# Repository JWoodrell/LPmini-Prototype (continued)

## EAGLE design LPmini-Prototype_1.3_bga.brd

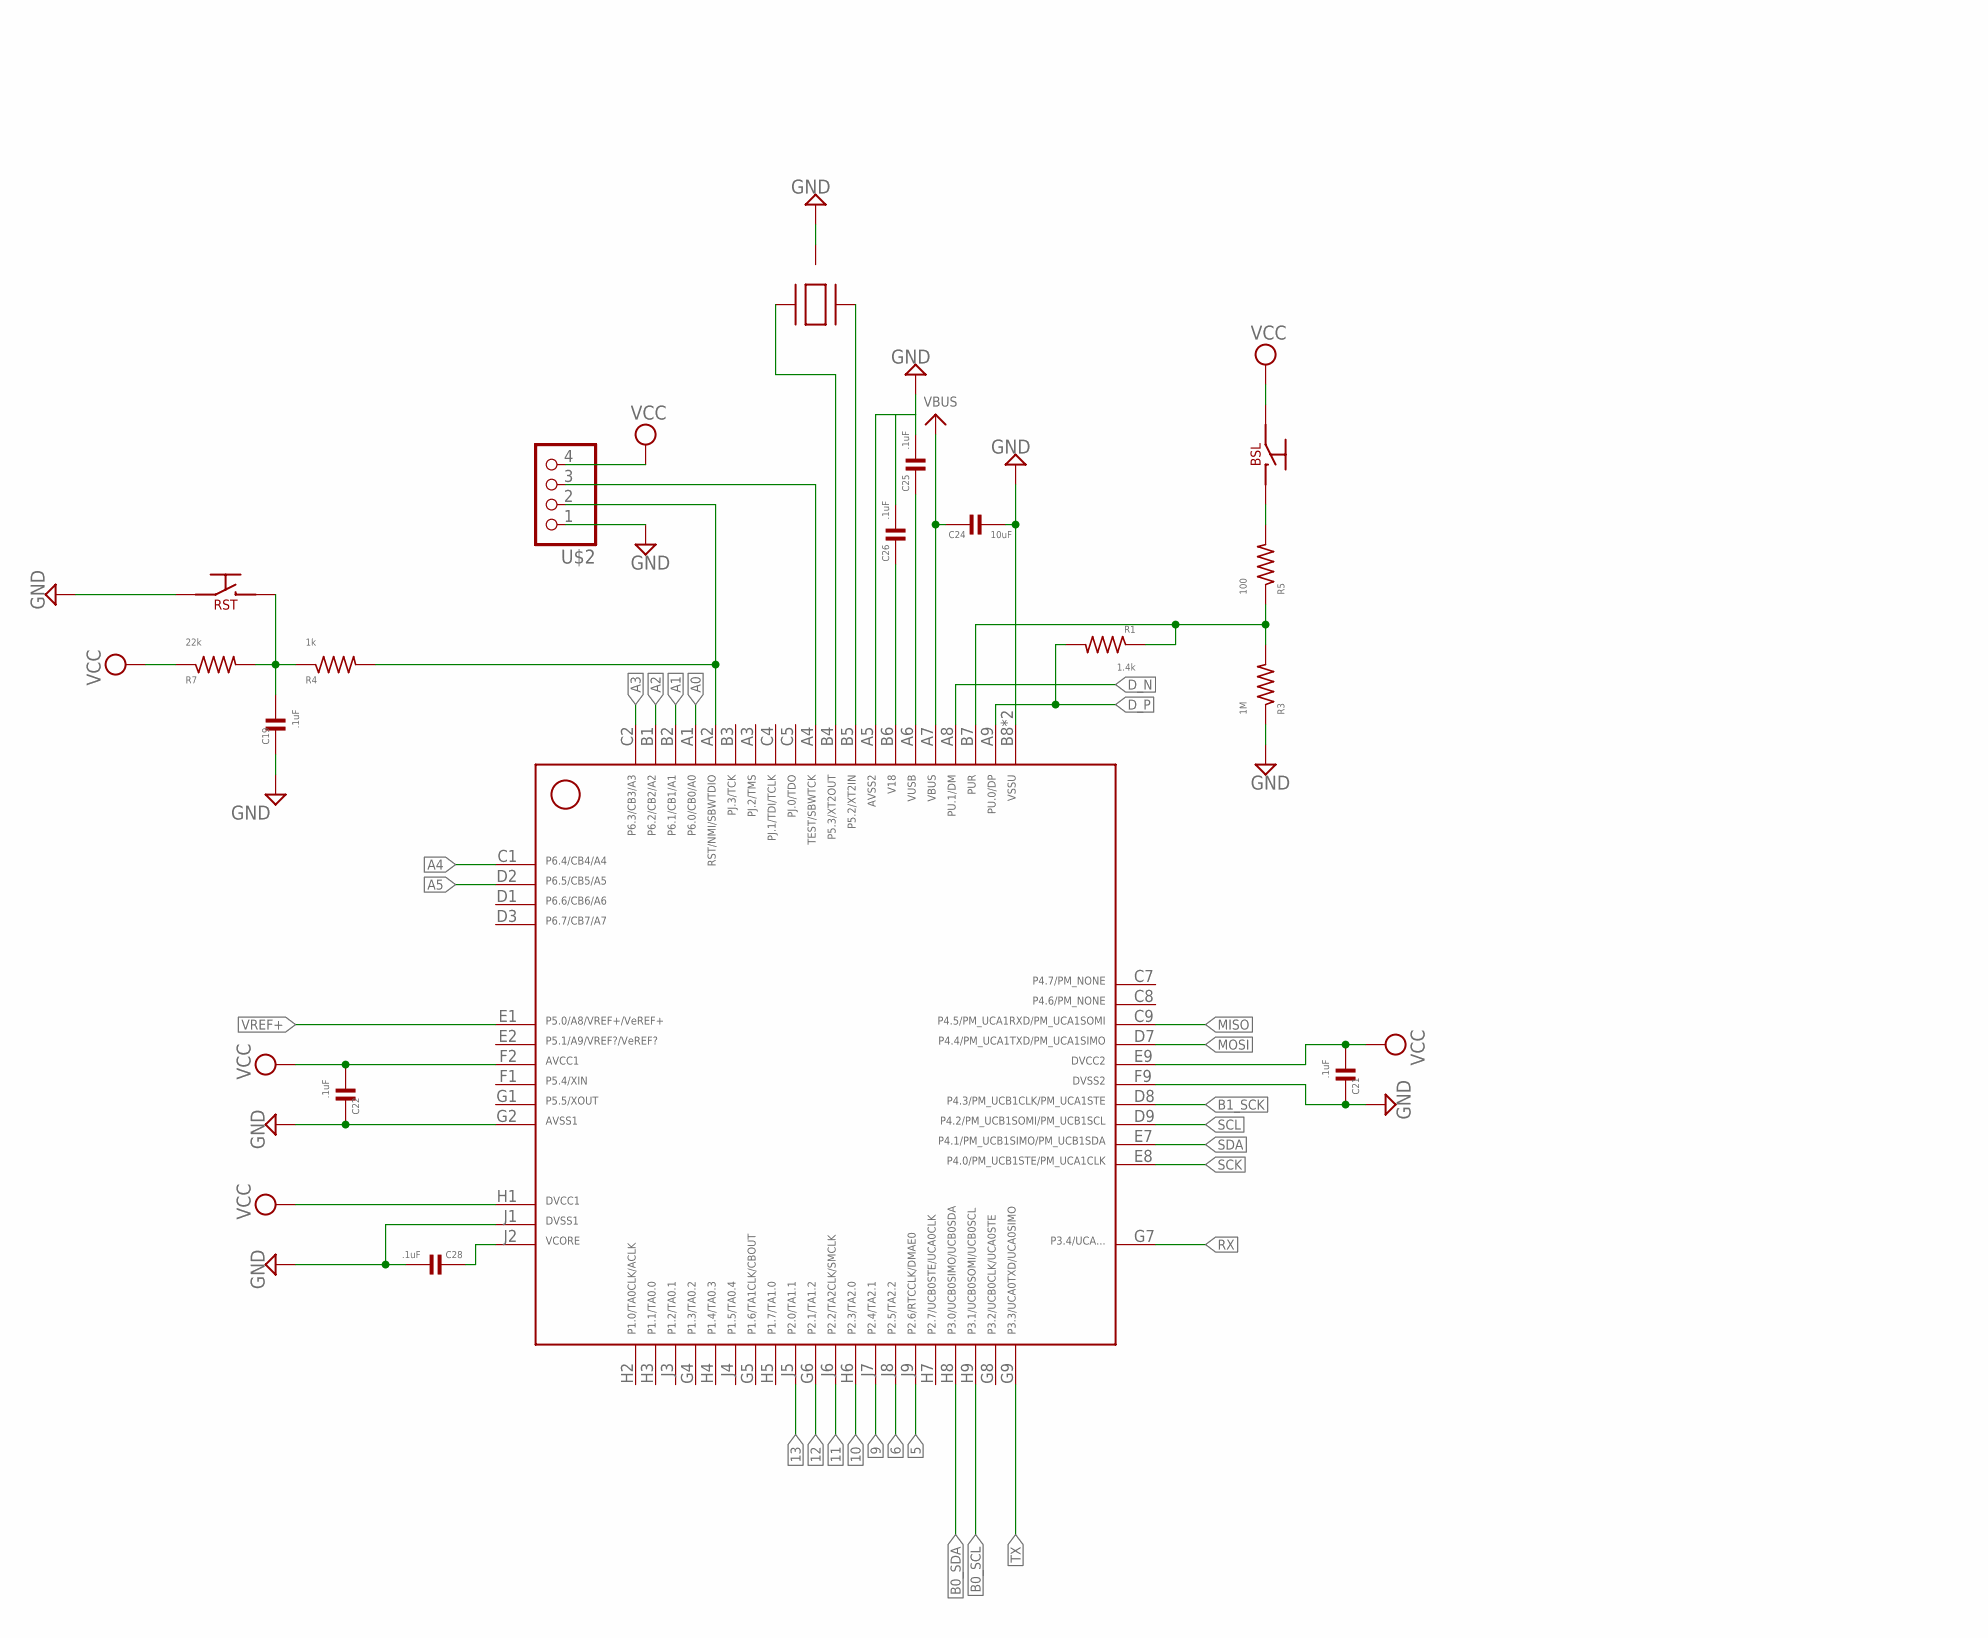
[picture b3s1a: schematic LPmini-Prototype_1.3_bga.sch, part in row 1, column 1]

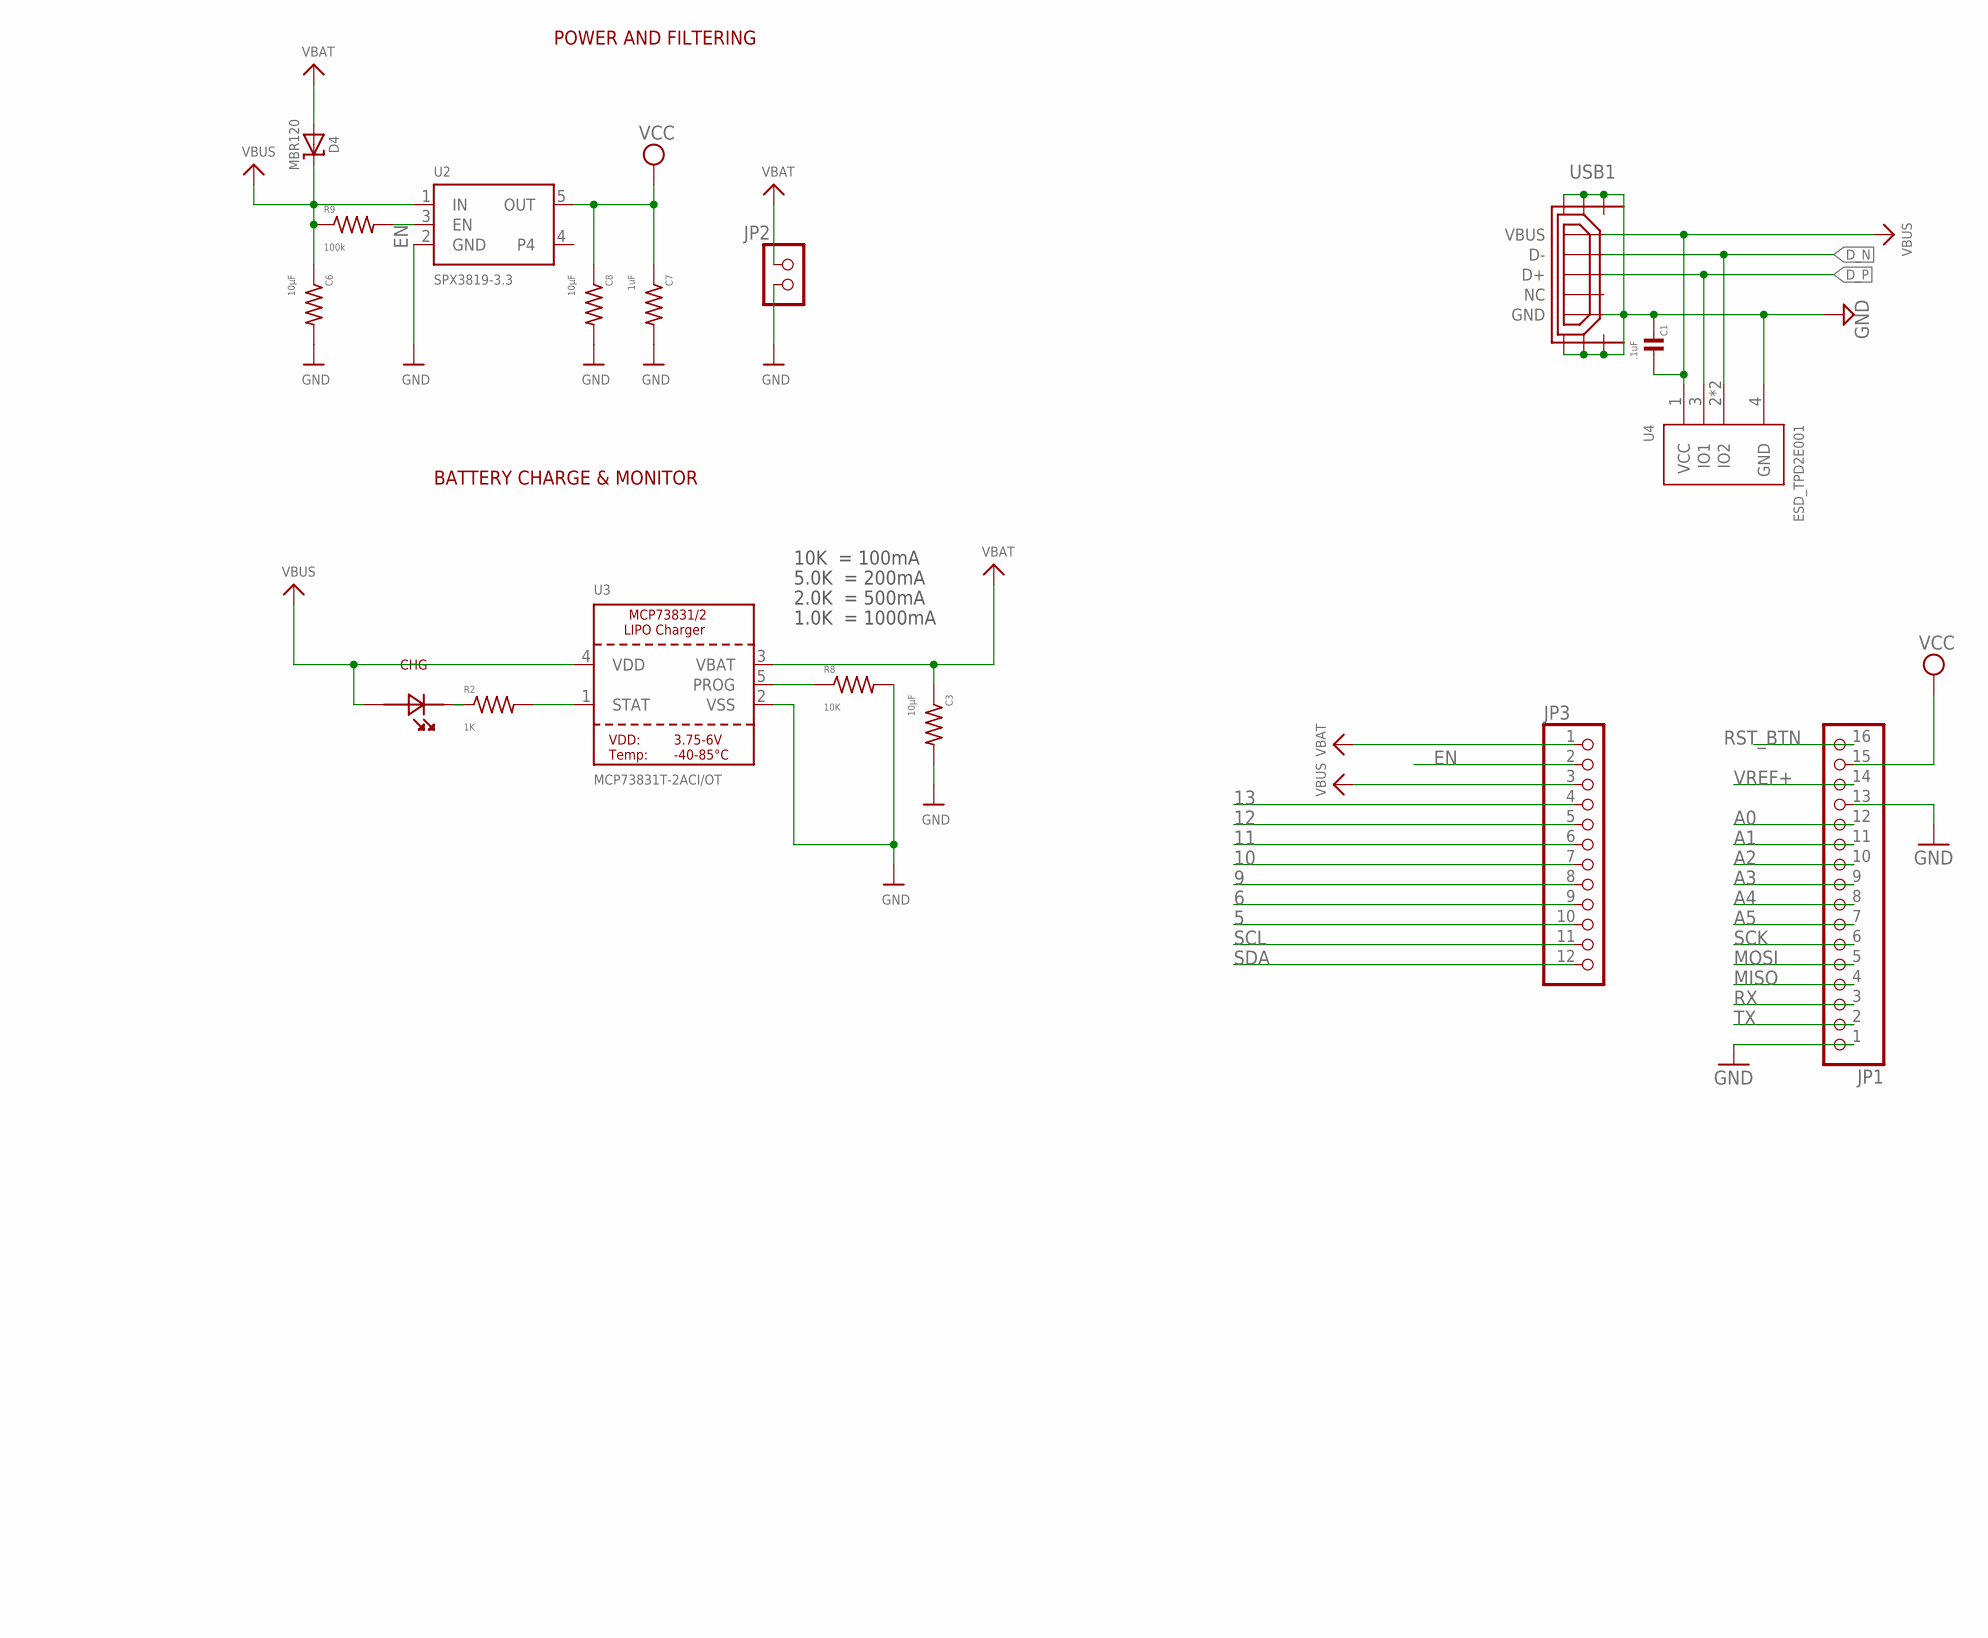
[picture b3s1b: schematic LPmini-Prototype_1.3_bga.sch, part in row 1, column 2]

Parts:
BSL: PB_SMALL_SMD; PB_KMR2
C1, C19, C21, C22, C25, C26, C28: .1uF; C0402
C3, C6, C8: 10µF; R0603
C7: 1uF; R0402
C24: 10uF; C0603
CHG: ORANGE; LED_0603
D4: MBR120; SOD-123
JP1: HEADER-1X16ROUND; 1X16_ROUND
JP2: 0_JOSEPH_PINHD-1X2END; 0_JOSEPH_1X02-END
JP3: HEADER-1X12; 1X12_ROUND
R1: 1.4k; R0402
R2: 1K; R0402
R3: 1M; R0402
R4: 1k; R0402
R5: 100; R0402
R7: 22k; R0402
R8: 10K; R0402
R9: 100k; R0402
RST: PB_SMALL_SMD; PB_KMR2
U2: SPX3819-3.3; SOT23-5
U3: MCP73831T-2ACI/OT; SOT23-5
U4: ESD_TPD2E001; PROJECT7264_TPD2E001-DRL
U$2: PINHD_1X4MOLEX_4_1MM; MOLEX_4_1MM
U$4: MSP430F5528; 80_BGA_MICROSTAR
U$5: CRYSTAL_SMD; SMD_CRYSTAL
USB1: USB_CON-UPDATE_USB_MICRO_FLIPPED; USB_CON-UPDATE_HIROSE-ZX62R-B-5P

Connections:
5: JP3.10, U$4.J9
6: JP3.9, U$4.J8
9: JP3.8, U$4.J7
10: JP3.7, U$4.H6
11: JP3.6, U$4.J6
12: JP3.5, U$4.G6
13: JP3.4, U$4.J5
A0: JP1.12, U$4.A1
A1: JP1.11, U$4.B2
A2: JP1.10, U$4.B1
A3: JP1.9, U$4.C2
A4: JP1.8, U$4.C1
A5: JP1.7, U$4.D2
B0_SCL: U$4.H9
B0_SDA: U$4.H8
B1_SCK: U$4.D8
D_N: U4.2 (IO2), U4.5 (IO2), U$4.A8, USB1.D-
D_P: R1.2, U4.3 (IO1), U$4.A9, USB1.D+
EN: JP3.2, R9.2, U2.3 (EN)
GND: C1.2, C3.2, C6.2, C7.2, C8.2, C19.2, C21.2, C22.2, C24.2, C25.2, C26.2, C28.2, JP1.1, JP1.13, JP2.2, R3.1, R8.2, RST.1A (A), RST.1B (A), U2.2 (GND), U3.2 (VSS), U4.4 (GND), U$2.1, U$4.A5, U$4.B8 (B8,B9), U$4.B9 (B8,B9), U$4.F9, U$4.G2, U$4.J1, U$5.2 (GND), U$5.4 (GND), USB1.GND, USB1.SHIELD1, USB1.SHIELD2, USB1.SHIELD3, USB1.SHIELD4, USB1.SHIELD5, USB1.SHIELD6
MISO: JP1.4, U$4.C9
MOSI: JP1.5, U$4.D7
unnamed: CHG.K (C), R2.1
unnamed: R2.2, U3.1 (STAT)
unnamed: R8.1, U3.5 (PROG)
unnamed: BSL.2A (B), BSL.2B (B), R5.2
unnamed: R1.1, R3.2, R5.1, U$4.B7
unnamed: U$2.3, U$4.A4
unnamed: U$4.B5, U$5.1
unnamed: U$4.B4, U$5.3
unnamed: C25.1, U$4.A6
unnamed: C26.1, U$4.B6
unnamed: C28.1, U$4.J2
RST: R4.2, U$2.2, U$4.A2
RST_BTN: C19.1, JP1.16, R4.1, R7.2, RST.2A (B), RST.2B (B)
RX: JP1.3, U$4.G7
SCK: JP1.6, U$4.E8
SCL: JP3.11, U$4.D9
SDA: JP3.12, U$4.E7
TX: JP1.2, U$4.G9
VBAT: C3.1, D4.A, JP2.1, JP3.1, U3.3 (VBAT)
VBUS: C1.1, C6.1, C24.1, CHG.A, D4.C, JP3.3, R9.1, U2.1 (IN), U3.4 (VDD), U4.1 (VCC), U$4.A7, USB1.VBUS
VCC: BSL.1A (A), BSL.1B (A), C7.1, C8.1, C21.1, C22.1, JP1.15, R7.1, U2.5 (OUT), U$2.4, U$4.E9, U$4.F2, U$4.H1
VREF+: JP1.14, U$4.E1

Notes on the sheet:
POWER AND FILTERING
10K = 100mA
5.0K = 200mA
2.0K = 500mA
1.0K = 1000mA
BATTERY CHARGE & MONITOR

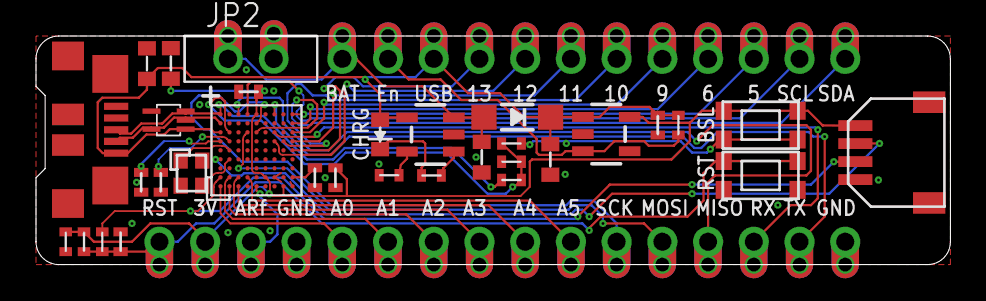
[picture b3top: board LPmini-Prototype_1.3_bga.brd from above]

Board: 2 copper layers, 50.8 x 12.7 mm, 35 parts (1 on the bottom side), 41 nets.

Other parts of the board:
U$7: TITAN_LOGO

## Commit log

2016-06-11 Rename LPmini-Prototype.brd to LPmini-Prototype_1.1.brd
2016-06-11 Rename LPmini-Prototype.sch to LPmini-Prototype_1.1.sch
2016-06-11 Rename LPmini-Prototype_1.1.sch to LPmini-Prototype_1.1/LPmini-Prototype_1.1.sch
2016-06-11 Rename LPmini-Prototype_1.1.brd to LPmini-Prototype_1.1/LPmini-Prototype_1.1.brd
2016-06-11 Rename LPmini-Prototype_1.2.brd to LPmini-Prototype_1.2/LPmini-Prototype_1.2.brd
2016-06-11 Rename LPmini-Prototype_1.2.sch to LPmini-Prototype_1.2/LPmini-Prototype_1.2.sch
2016-06-15 Rename LPmini-Prototype_1.3_bga.brd to LPmini-Prototype_1.3_bga/LPmini-Prototype_1.3_bga.brd
2016-06-15 Rename LPmini-Prototype_1.3_bga.sch to LPmini-Prototype_1.3_bga/LPmini-Prototype_1.3_bga.sch
2016-06-22 Rename LPmini-Prototype_1.4.brd to LPmini-Prototype_1.4/LPmini-Prototype_1.4.brd
2016-06-22 Rename LPmini-Prototype_1.4.sch to LPmini-Prototype_1.4/LPmini-Prototype_1.4.sch
